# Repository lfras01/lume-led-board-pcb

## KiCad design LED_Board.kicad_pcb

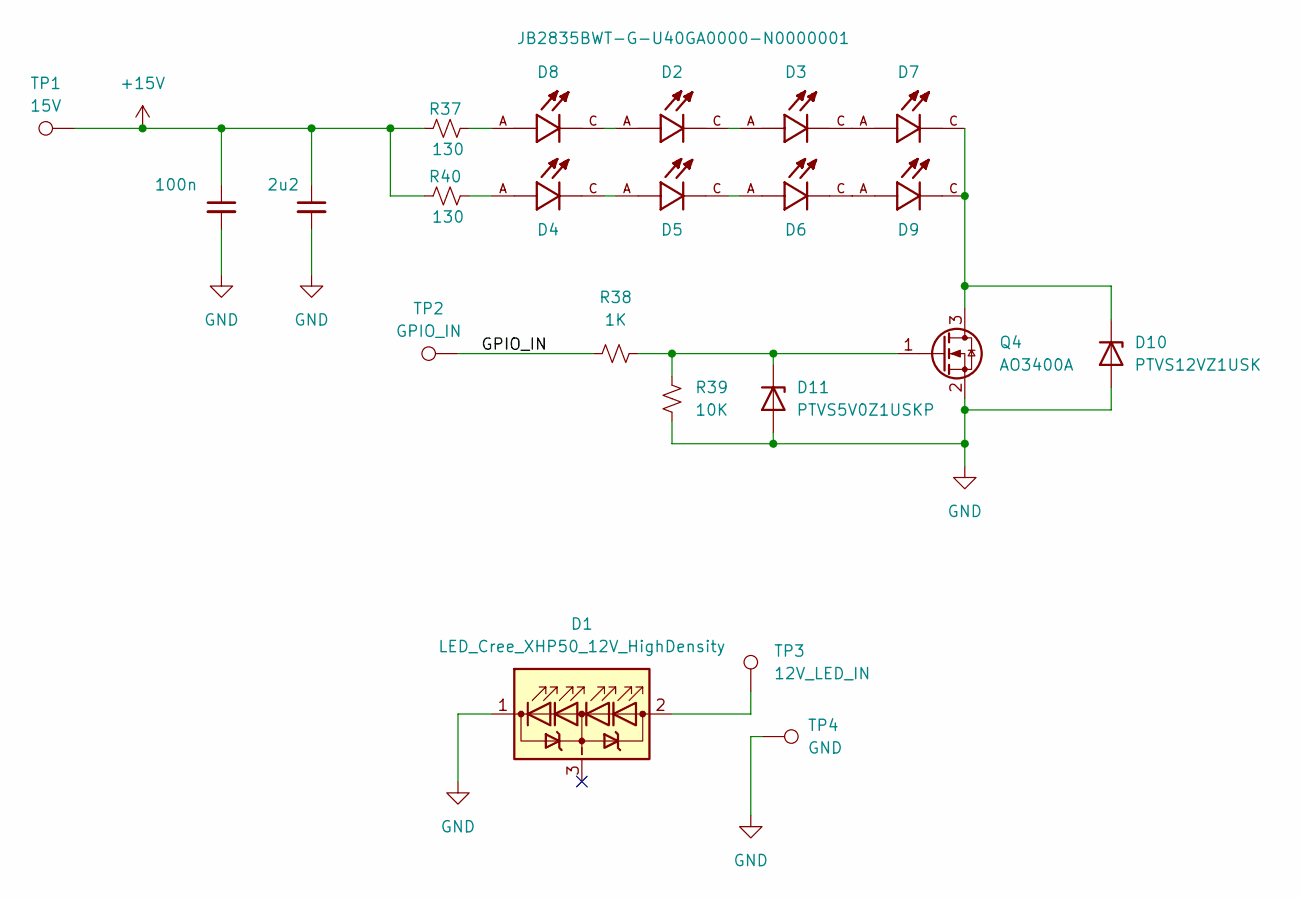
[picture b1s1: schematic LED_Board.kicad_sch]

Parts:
C1: 100n; C_0805_2012Metric; MPN CC0805KRX7R9BB104
C2: 2u2; C_0805_2012Metric; MPN GRM188R61E225KA12D
D1: LED_Cree_XHP50_12V_HighDensity; LED_Cree-XHP50_12V_HighDensity; MPN XHP50D-H0-0000-0D0ZE427G
D2, D3, D4, D5, D6, D7, D8, D9: JB2835BWT-G-U40GA0000-N0000001; LED_JB2835BWT-G-U40GA0000-N0000001; PARTREV 3A
D10: PTVS12VZ1USK; Nexperia_DSN1608-2_1.6x0.8mm; MPN PTVS12VZ1USKYL
D11: PTVS5V0Z1USKP; Nexperia_DSN1608-2_1.6x0.8mm; MPN PTVS5V0Z1USKPYL
Q4: AO3400A; SOT-23; MPN AO3400A
R37, R40: 130; R_0805_2012Metric; MPN RMCF0805FT130R
R38: 1K; R_0805_2012Metric; MPN RMCF0805FT1K00
R39: 10K; R_0805_2012Metric; MPN RMCF0805FT10K0
TP1: 15V; TestPoint_Pad_2.0x2.0mm
TP2: GPIO_IN; TestPoint_Pad_2.0x2.0mm
TP3: 12V_LED_IN; TestPoint_Pad_2.0x2.0mm
TP4: GND; TestPoint_Pad_2.0x2.0mm

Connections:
+15V: C1.1, C2.1, R37.2, R40.2, TP1.1 (1_1)
/GPIO_IN: R38.1, TP2.1 (1_1)
GND: C1.2, C2.2, D1.1 (K), D10.2 (A), D11.2 (A), Q4.2 (S), R39.1, TP4.1 (1_1)
unnamed: D1.2 (A), TP3.1 (1_1)
unnamed: D2.A, D8.C
unnamed: D2.C, D3.A
unnamed: D3.C, D7.A
unnamed: D4.A, R40.1
unnamed: D4.C, D5.A
unnamed: D5.C, D6.A
unnamed: D6.C, D9.A
unnamed: D8.A, R37.1
unnamed: D7.C, D9.C, D10.1 (K), Q4.3 (D)
unnamed: D11.1 (K), Q4.1 (G), R38.2, R39.2

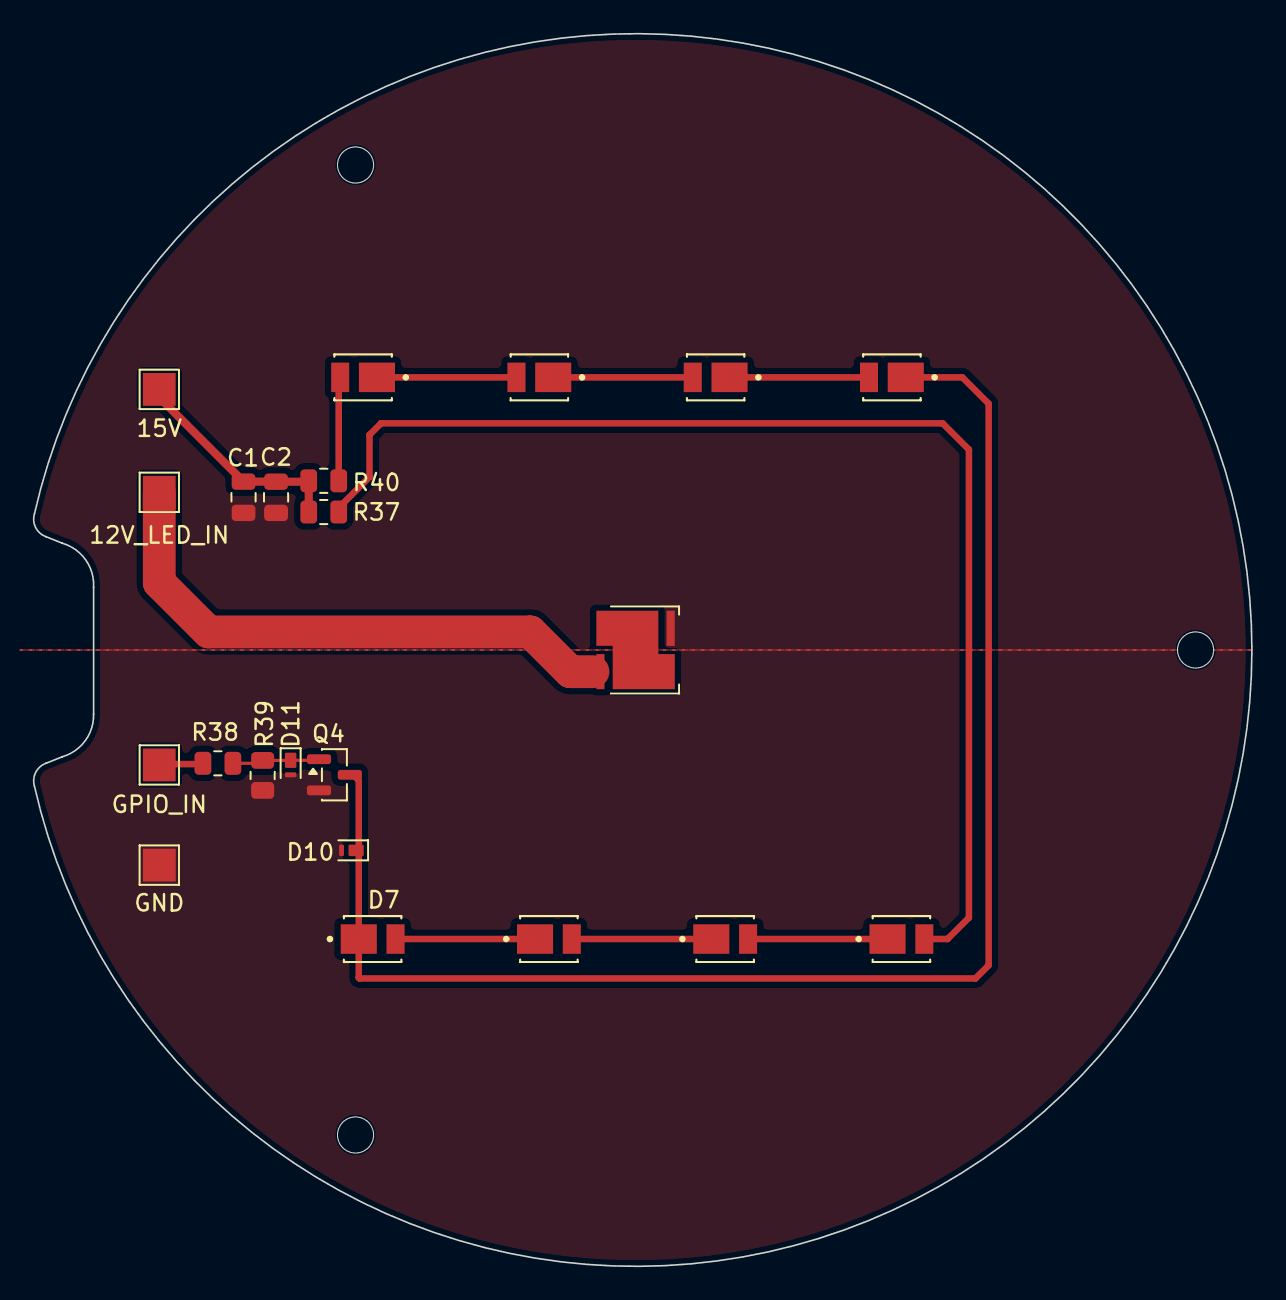
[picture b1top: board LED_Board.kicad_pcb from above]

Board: 2 copper layers, 74.2 x 75.1 mm, 22 parts (0 on the bottom side), 14 nets.

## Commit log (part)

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2026-03-23 Initial Board Design
2026-03-29 Added 6 Warm LEDS and cleanup of silkscreen
2026-04-06 Added LEDs and fixed V_IN trace widths
2026-04-07 finalised
2026-05-07 Apply all Fixes from Rev 1 (First Pass)
2026-05-10 Release 1.1.0
2026-06-02 Reorganize LED_Board project structure
2026-06-02 Move
